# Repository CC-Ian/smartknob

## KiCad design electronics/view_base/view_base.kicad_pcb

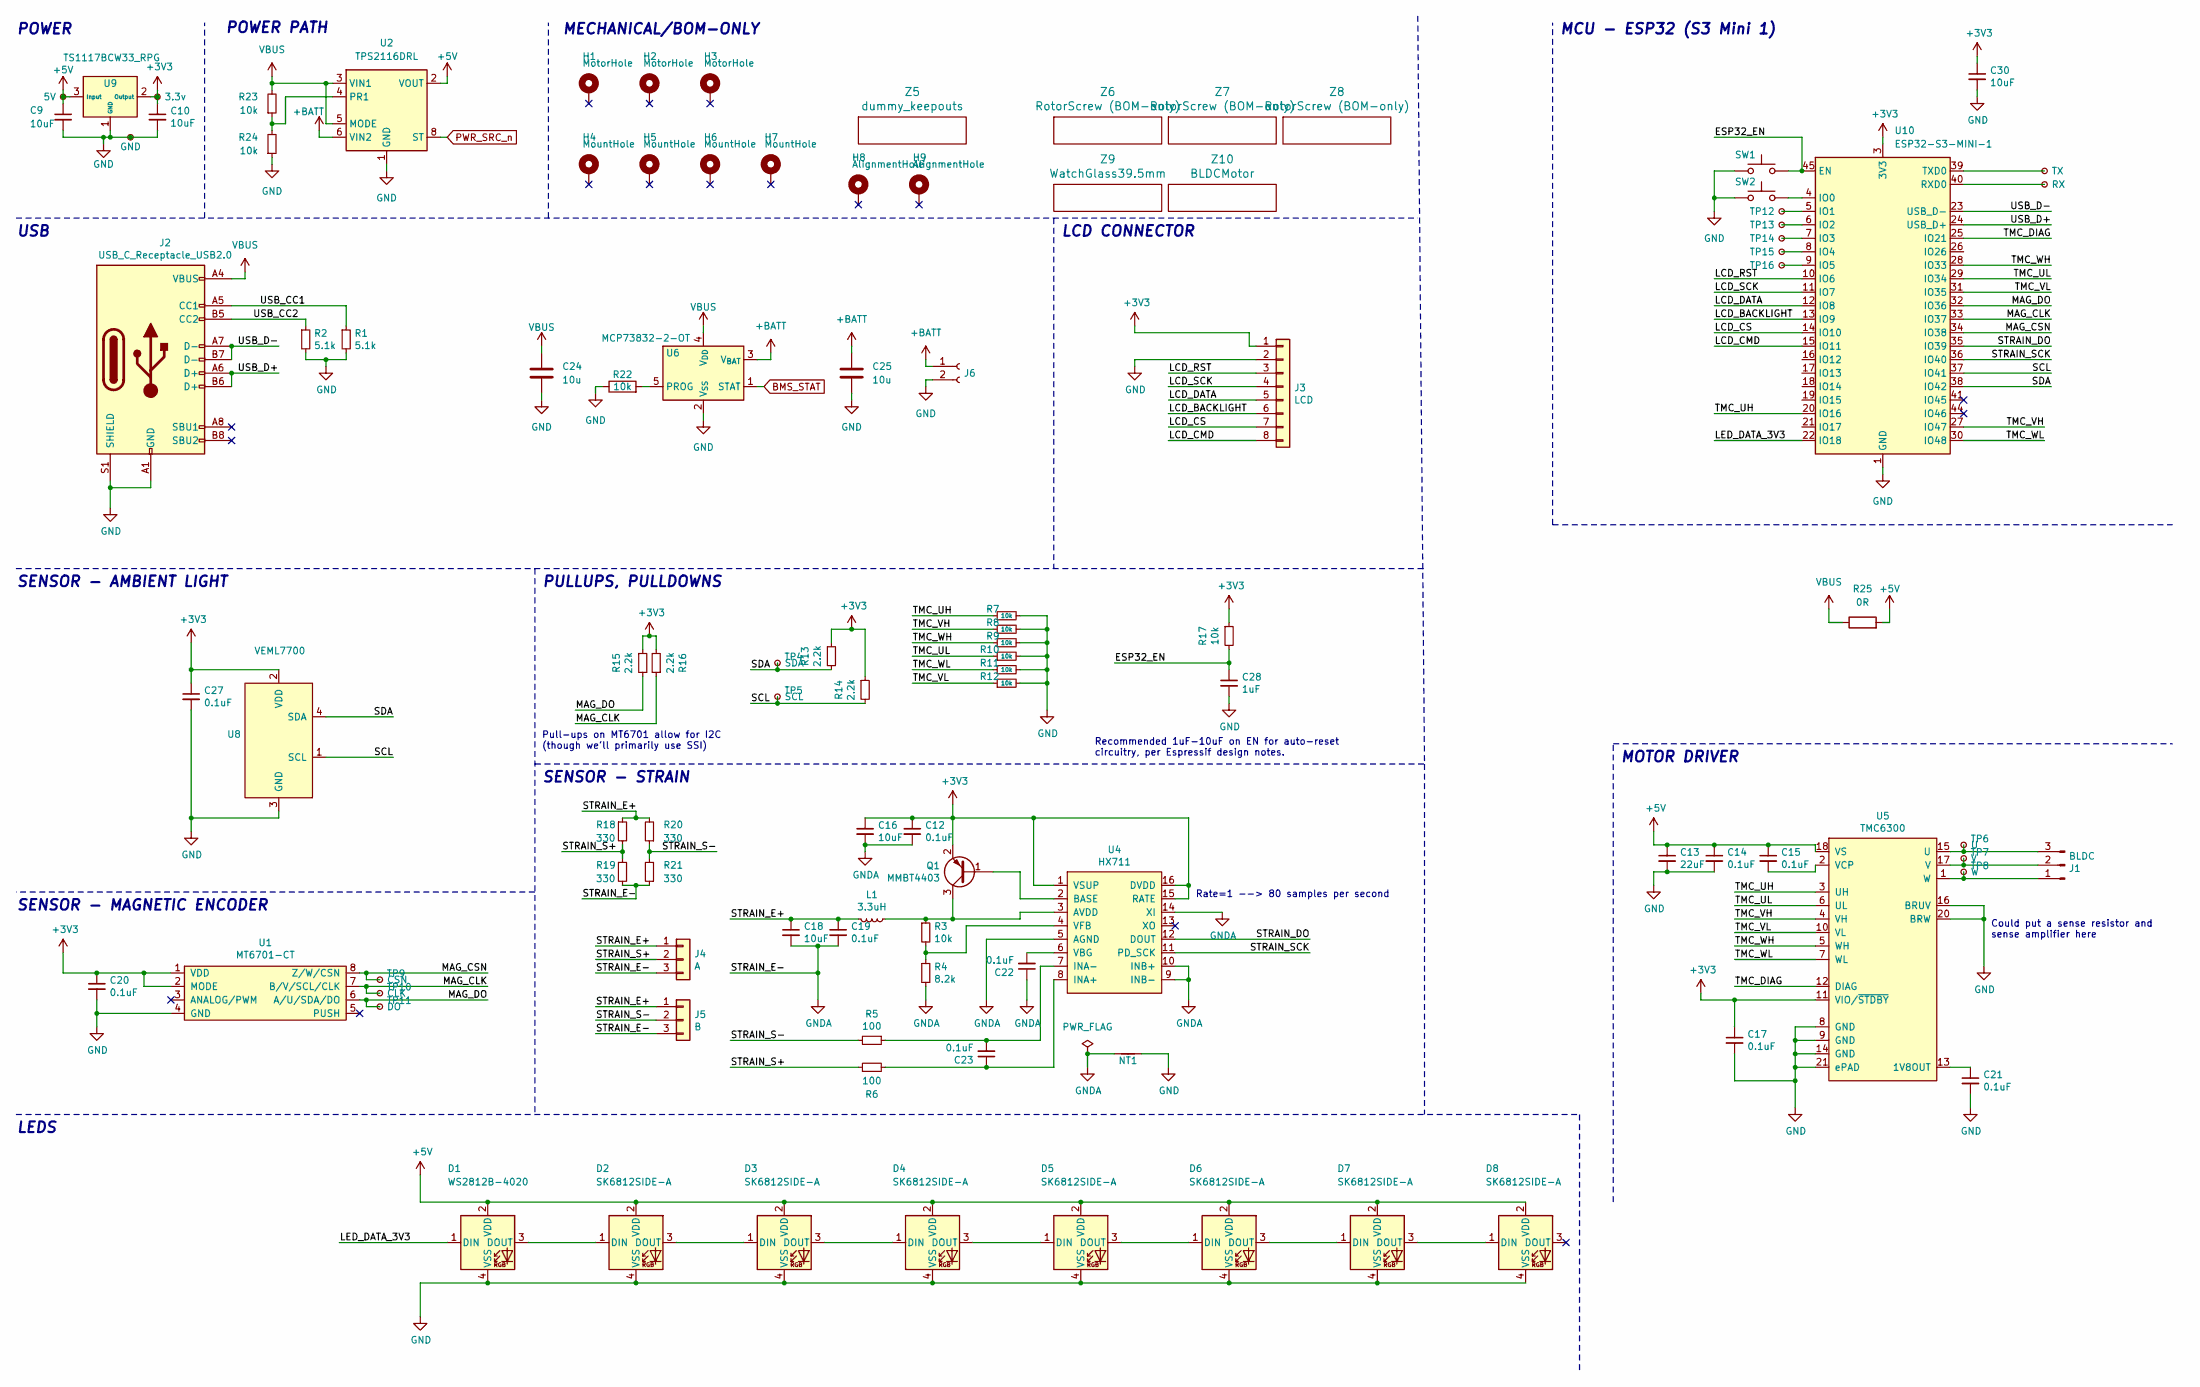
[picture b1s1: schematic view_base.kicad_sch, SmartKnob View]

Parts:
C9, C10, C16, C18, C30: 10uF; C_0603_1608Metric; LCSC C2922480
C12, C14, C15, C17, C19, C20, C21, C22, C23, C27: 0.1uF; C_0402_1005Metric; LCSC C1591
C13: 22uF; C_0603_1608Metric; LCSC C98190
C24, C25: 10u; C_0603_1608Metric
C28: 1uF; C_0402_1005Metric; Mouser 187-CL10A105KA8NNNC
D1: WS2812B-4020; WS2812B4020; Digikey 1528-4691-ND
D2, D3, D4, D5, D6, D7, D8: SK6812SIDE-A; WS2812B4020; Digikey 1528-4691-ND
H1, H2, H3: MotorHole; MountingHole_M1.6; LCSC C2931389
H4, H5, H6, H7: MountHole; MountingHole_2.2mm_M2_ISO7380_Pad_NonVirtual; LCSC C2911210 or C2911532 (screw), C2961595 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
H8, H9: AlignmentHole; MountingHole_2.2mm_M2_ISO7380_Pad_NonVirtual
J1: BLDC; 532610371; LCSC C293630
J2: USB_C_Receptacle_USB2.0; USB4510_NoPaste; LCSC C428463
J3: LCD; SolderPads_2mm_8
J4: A; SolderPads_2mm_3_STRAIN
J5: B; SolderPads_2mm_3_STRAIN
J6: Conn_01x02_Socket; PinHeader_1x02_P2.00mm_Vertical
L1: 3.3uH; L_0603_1608Metric; LCSC C307744
NT1: NetTie_2; NetTie-2_SMD_Pad0.5mm
Q1: MMBT4403; SOT-23; LCSC C78864
R1, R2: 5.1k; R_0402_1005Metric; LCSC C105580
R3, R7, R8, R9, R10, R11, R12, R17: 10k; R_0402_1005Metric; LCSC C98220
R4: 8.2k; R_0402_1005Metric; LCSC C114637
R5, R6: 100; R_0402_1005Metric; LCSC C319953
R13, R14, R15, R16: 2.2k; R_0402_1005Metric; LCSC C4190
R18, R19, R20, R21: 330; R_2512_6332Metric; LCSC C19866
R22, R23, R24: 10k; R_0402_1005Metric
R25: 0R; R_0603_1608Metric
SW1, SW2: SW_Push; T1B2QR
TP1: 5V; TestPoint_Pad_D2.0mm_ValueSilk
TP2: 3.3v; TestPoint_Pad_D2.0mm_ValueSilk
TP3: GND; TestPoint_Pad_D2.0mm_ValueSilk
TP4: SDA; TestPoint_Pad_D2.0mm_ValueSilk
TP5: SCL; TestPoint_Pad_D2.0mm_ValueSilk
TP6: U; TestPoint_Pad_D2.0mm_ValueSilk
TP7: V; TestPoint_Pad_D2.0mm_ValueSilk
TP8: W; TestPoint_Pad_D2.0mm_ValueSilk
TP9: CSN; TestPoint_Pad_D2.0mm_ValueSilk
TP10: CLK; TestPoint_Pad_D2.0mm_ValueSilk
TP11: DO; TestPoint_Pad_D2.0mm_ValueSilk
TP12, TP13, TP14, TP15, TP16: TestPoint_Small; TestPoint_Pad_D1.0mm
TP17: TX; TestPoint_Pad_D2.0mm_ValueSilk
TP18: RX; TestPoint_Pad_D2.0mm_ValueSilk
U1: MT6701-CT; SOIC-8_3.9x4.9mm_P1.27mm; LCSC C2856764, or C3003196
U2: TPS2116DRL; SOT-583-8; LCSC C3235557
U4: HX711; SOIC-16_3.9x9.9mm_P1.27mm; LCSC C43656
U5: TMC6300; QFN-20-1EP_3x3mm_P0.4mm_EP1.65x1.65mm; Digikey TMC6300-LA-T
U6: MCP73832-2-OT; SOT-23-5; LCSC C38066
U8: VEML7700; VEML7700-TOP; Digikey VEML7700-TT
U9: TS1117BCW33_RPG; SOT-223-3_TabPin2_GndOutIn; LCSC C6186
U10: ESP32-S3-MINI-1; ESP32-S2-MINI-1; LCSC C2913206
Z5: dummy_keepouts; ViewKeepouts3d
Z6, Z7, Z8: RotorScrew (BOM-only); bom_only_no_pin
Z9: WatchGlass39.5mm; bom_only_no_pin
Z10: BLDCMotor; bom_only_no_pin

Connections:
+3V3: C10.1, C12.1, C16.1, C17.1, C20.1, C27.1, C30.1, J3.1, Q1.2 (E), R13.1, R14.1, R15.1, R16.2, R17.1, TP2.1, U1.1 (VDD), U1.2 (MODE), U4.1 (VSUP), U4.15 (RATE), U4.16 (DVDD), U5.11 (VIO/~STDBY), U8.2 (VDD), U9.2 (Output), U10.3 (3V3)
+5V: C9.1, C13.1, C14.1, C15.1, D1.2 (VDD), D2.2 (VDD), D3.2 (VDD), D4.2 (VDD), D5.2 (VDD), D6.2 (VDD), D7.2 (VDD), D8.2 (VDD), R25.2, TP1.1, U2.2 (VOUT), U2.7 (VOUT), U5.18 (VS), U9.3 (Input)
+BATT: C25.1, J6.1, U2.6 (VIN2), U6.3 (V_{BAT})
/ESP32_EN: C28.1, R17.2, SW1.2, U10.45 (EN)
/LCD_BACKLIGHT: J3.6, U10.13 (IO9)
/LCD_CMD: J3.8, U10.15 (IO11)
/LCD_CS: J3.7, U10.14 (IO10)
/LCD_DATA: J3.5, U10.12 (IO8)
/LCD_RST: J3.3, U10.10 (IO6)
/LCD_SCK: J3.4, U10.11 (IO7)
/LED_DATA_3V3: D1.1 (DIN), U10.22 (IO18)
/MAG_CLK: R16.1, TP10.1, U1.7 (B/V/SCL/CLK), U10.33 (IO37)
/MAG_CSN: TP9.1, U1.8 (Z/W/CSN), U10.34 (IO38)
/MAG_DO: R15.2, TP11.1, U1.6 (A/U/SDA/DO), U10.32 (IO36)
/SCL: R14.2, TP5.1, U8.1 (SCL), U10.37 (IO41)
/SDA: R13.2, TP4.1, U8.4 (SDA), U10.38 (IO42)
/STRAIN_DO: U4.12 (DOUT), U10.35 (IO39)
/STRAIN_E+: C18.1, C19.1, J4.1, J5.1, L1.2, R18.1, R20.2
/STRAIN_S+: J4.2, R6.1, R18.2, R19.1
/STRAIN_S-: J5.2, R5.2, R20.1, R21.2
/STRAIN_SCK: U4.11 (PD_SCK), U10.36 (IO40)
/TMC_DIAG: U5.12 (DIAG), U10.25 (IO21)
/TMC_UH: R7.1, U5.3 (UH), U10.20 (IO16)
/TMC_UL: R10.1, U5.6 (UL), U10.29 (IO34)
/TMC_VH: R8.1, U5.4 (VH), U10.27 (IO47)
/TMC_VL: R12.1, U5.10 (VL), U10.31 (IO35)
/TMC_WH: R9.1, U5.5 (WH), U10.28 (IO33)
/TMC_WL: R11.1, U5.7 (WL), U10.30 (IO48)
/USB_CC1: J2.A5 (CC1), R1.1
/USB_CC2: J2.B5 (CC2), R2.1
/USB_D+: J2.A6 (D+), J2.B6 (D+), U10.24 (USB_D+)
/USB_D-: J2.A7 (D-), J2.B7 (D-), U10.23 (USB_D-)
BMS_STAT: U6.1 (STAT)
GND: C9.2, C10.2, C13.2, C14.2, C17.2, C20.2, C21.2, C24.2, C25.2, C27.2, C28.2, C30.2, D1.4 (VSS), D2.4 (VSS), D3.4 (VSS), D4.4 (VSS), D5.4 (VSS), D6.4 (VSS), D7.4 (VSS), D8.4 (VSS), J2.A1 (GND), J2.A12 (GND), J2.B1 (GND), J2.B12 (GND), J2.S1 (SHIELD), J3.2, J6.2, NT1.2, R1.2, R2.2, R7.2, R8.2, R9.2, R10.2, R11.2, R12.2, R22.1, R24.1, SW1.1, SW2.1, TP3.1, U1.4 (GND), U2.1 (GND), U5.8 (GND), U5.9 (GND), U5.14 (GND), U5.16 (BRUV), U5.20 (BRW), U5.21 (ePAD), U6.2 (V_{SS}), U8.3 (GND), U9.1 (GND), U10.1 (GND), U10.2 (GND), U10.42 (GND), U10.43 (GND), U10.46 (GND), U10.47 (GND), U10.48 (GND), U10.49 (GND), U10.50 (GND), U10.51 (GND), U10.52 (GND), U10.53 (GND), U10.54 (GND), U10.55 (GND), U10.56 (GND), U10.57 (GND), U10.58 (GND), U10.59 (GND), U10.60 (GND), U10.61 (GND), U10.62 (GND), U10.63 (GND), U10.64 (GND), U10.65 (GND)
GNDA: C12.2, C16.2, C18.2, C19.2, C22.1, J4.3, J5.3, NT1.1, R4.2, R19.2, R21.1, U4.5 (AGND), U4.9 (INB-), U4.10 (INB+), U4.14 (XI)
unnamed: D1.3 (DOUT), D2.1 (DIN)
unnamed: D2.3 (DOUT), D3.1 (DIN)
unnamed: D3.3 (DOUT), D4.1 (DIN)
unnamed: D4.3 (DOUT), D5.1 (DIN)
unnamed: D5.3 (DOUT), D6.1 (DIN)
unnamed: D6.3 (DOUT), D7.1 (DIN)
unnamed: D7.3 (DOUT), D8.1 (DIN)
unnamed: J1.1, TP8.1, U5.1 (W)
unnamed: J1.2, TP7.1, U5.17 (V)
unnamed: J1.3, TP6.1, U5.15 (U)
unnamed: Q1.1 (B), U4.2 (BASE)
unnamed: L1.1, Q1.3 (C), R3.1, U4.3 (AVDD)
unnamed: R23.1, R24.2, U2.4 (PR1)
unnamed: C23.1, R6.2, U4.8 (INA+)
unnamed: C23.2, R5.1, U4.7 (INA-)
unnamed: C22.2, U4.6 (VBG)
unnamed: R3.2, R4.1, U4.4 (VFB)
unnamed: C21.1, U5.13 (1V8OUT)
unnamed: C15.2, U5.2 (VCP)
unnamed: R22.2, U6.5 (PROG)
unnamed: SW2.2, U10.4 (IO0)
unnamed: TP12.1, U10.5 (IO1)
unnamed: TP13.1, U10.6 (IO2)
unnamed: TP14.1, U10.7 (IO3)
unnamed: TP15.1, U10.8 (IO4)
unnamed: TP16.1, U10.9 (IO5)
unnamed: TP18.1, U10.40 (RXD0)
unnamed: TP17.1, U10.39 (TXD0)
PWR_SRC_n: U2.8 (ST)
VBUS: C24.1, J2.A4 (VBUS), J2.A9 (VBUS), J2.B4 (VBUS), J2.B9 (VBUS), R23.2, R25.1, U2.3 (VIN1), U2.5 (MODE), U6.4 (V_{DD})

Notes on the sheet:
POWER PATH
MECHANICAL/BOM-ONLY
USB
Could put a sense resistor and sense amplifier here
Pull-ups on MT6701 allow for I2C (though we'll primarily use SSI)
SENSOR - MAGNETIC ENCODER
PULLUPS, PULLDOWNS
LEDS
Recommended 1uF-10uF on EN for auto-reset circuitry, per Espressif design notes.
MCU - ESP32 (S3 Mini 1)
LCD CONNECTOR
POWER
Rate=1 --> 80 samples per second
MOTOR DRIVER
SENSOR - AMBIENT LIGHT
SENSOR - STRAIN

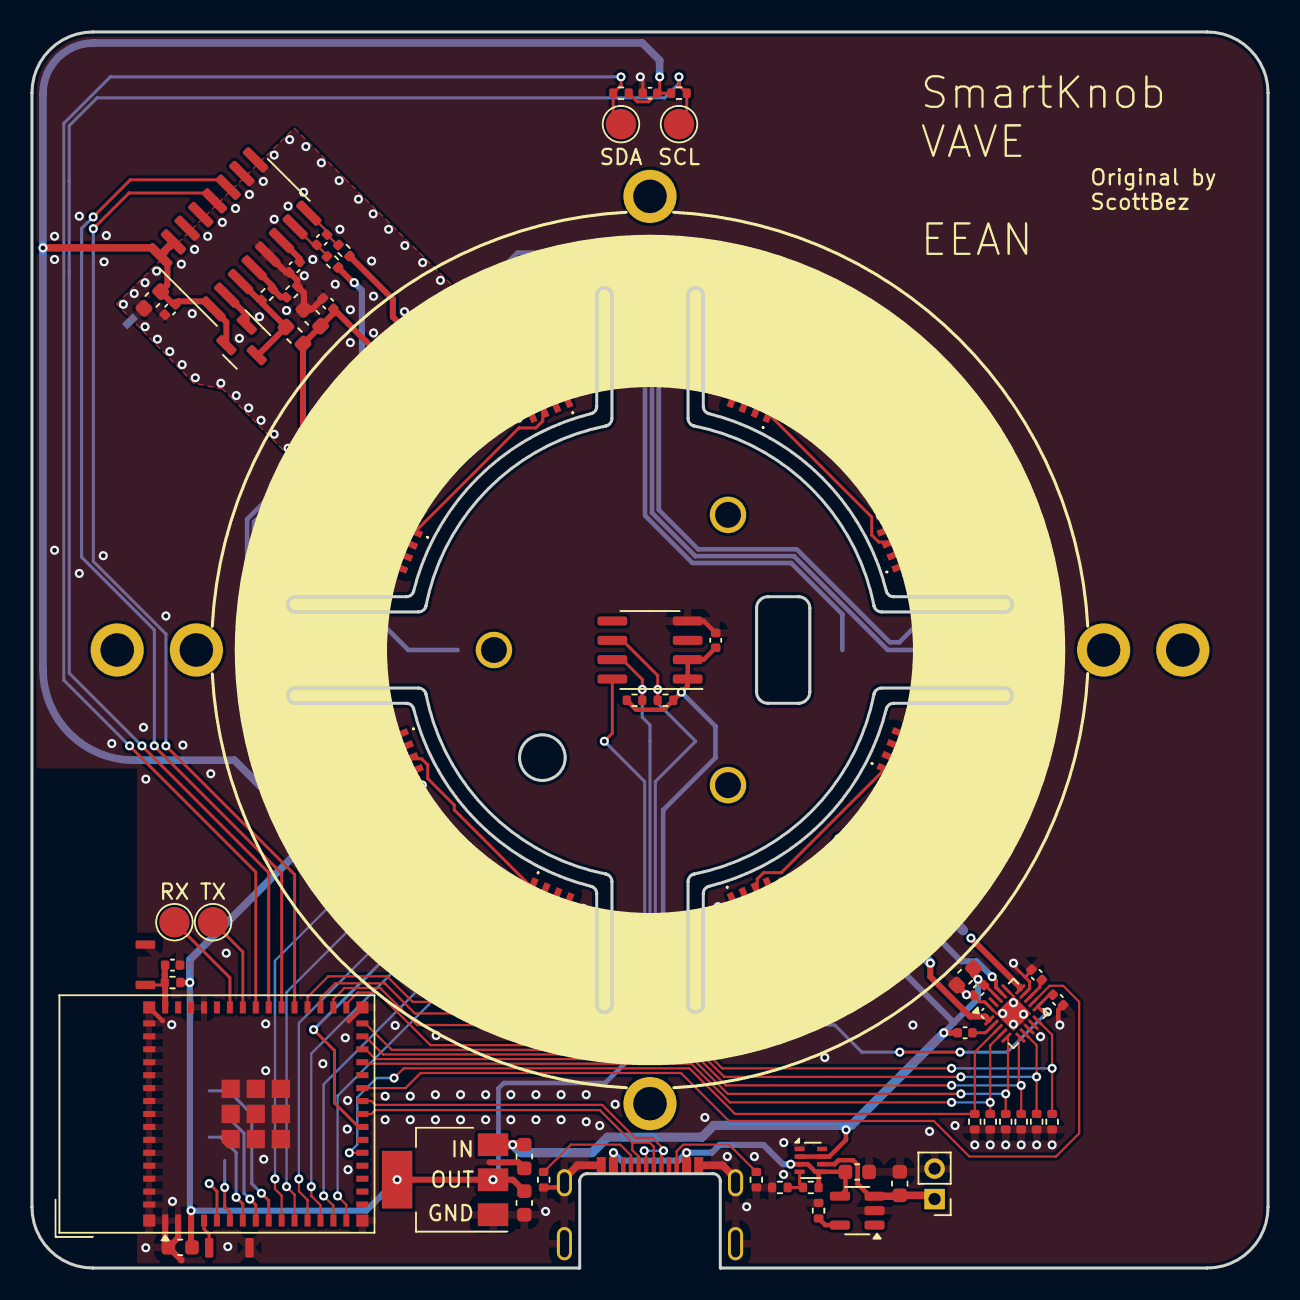
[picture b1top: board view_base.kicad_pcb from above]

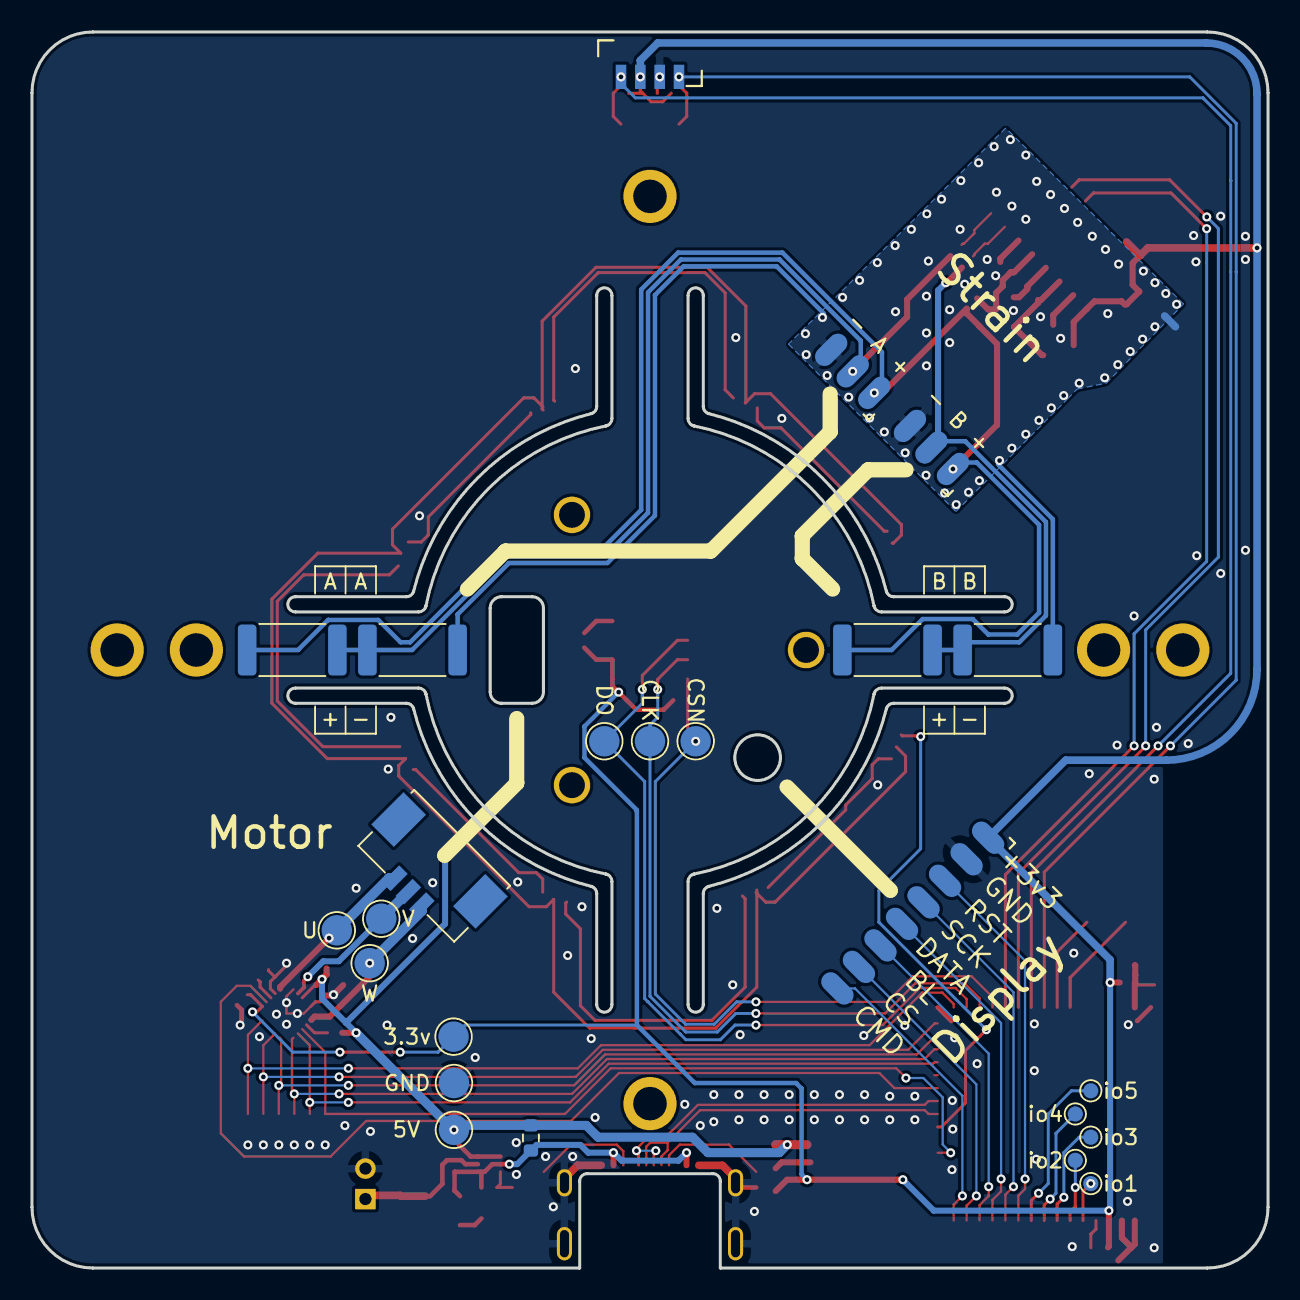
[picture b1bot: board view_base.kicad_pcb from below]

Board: 2 copper layers, 81.2 x 81.2 mm, 103 parts (25 on the bottom side), 63 nets.

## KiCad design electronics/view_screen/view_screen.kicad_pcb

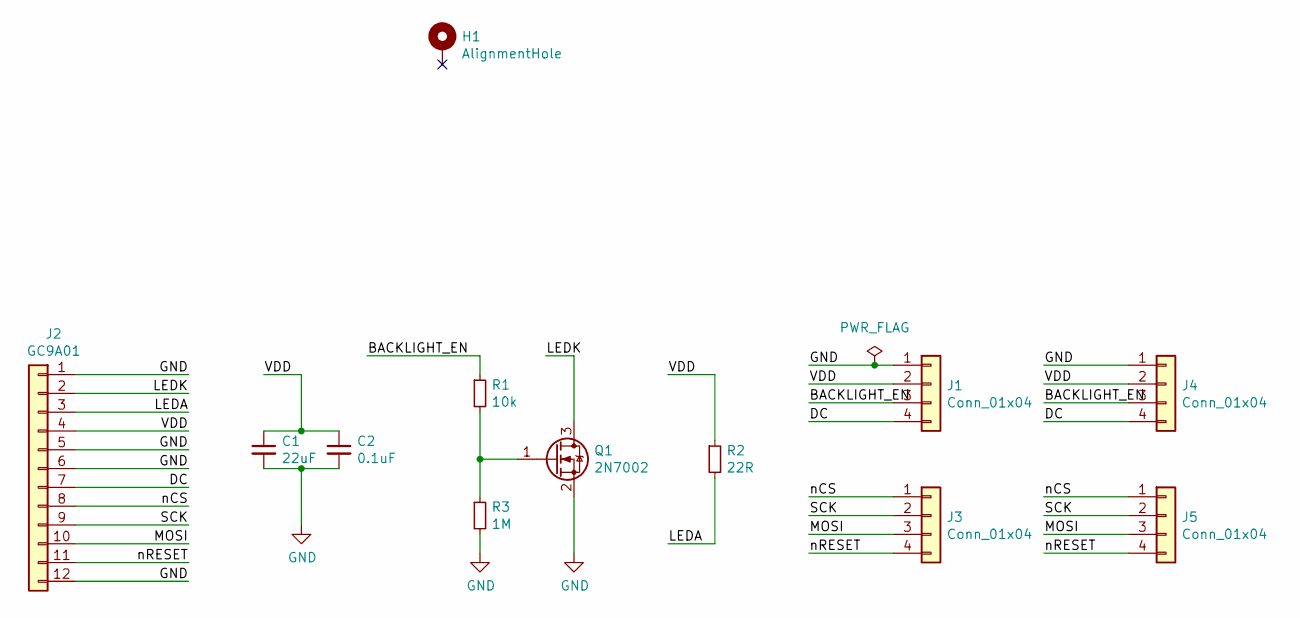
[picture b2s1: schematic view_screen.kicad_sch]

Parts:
C1: 22uF; C_0603_1608Metric; Digikey 1276-CL21A226MAYNNNECT-ND
C2: 0.1uF; C_0402_1005Metric; Digikey 1276-1935-1-ND
H1: AlignmentHole; AlignmentHole_1.6
J1, J3, J4, J5: Conn_01x04; SolderPads_2mm_4
J2: GC9A01; GC9A01Round1.28; Digikey N/A
Q1: 2N7002; SOT-23; Digikey 2N7002H6327XTSA2CT-ND
R1: 10k; R_0402_1005Metric; Digikey RMCF0603JT10K0CT-ND
R2: 22R; R_0402_1005Metric; Digikey RMCF0603JT22R0CT-ND
R3: 1M; R_0402_1005Metric; Digikey RMCF0603JT1M00CT-ND

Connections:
/BACKLIGHT_EN: J1.3, J4.3, R1.1
/DC: J1.4, J2.7, J4.4
/LEDA: J2.3, R2.2
/LEDK: J2.2, Q1.3 (D)
/MOSI: J2.10, J3.3, J5.3
/SCK: J2.9, J3.2, J5.2
/VDD: C1.1, C2.1, J1.2, J2.4, J4.2, R2.1
/nCS: J2.8, J3.1, J5.1
/nRESET: J2.11, J3.4, J5.4
GND: C1.2, C2.2, J1.1, J2.1, J2.5, J2.6, J2.12, J4.1, Q1.2 (S), R3.2
unnamed: Q1.1 (G), R1.2, R3.1

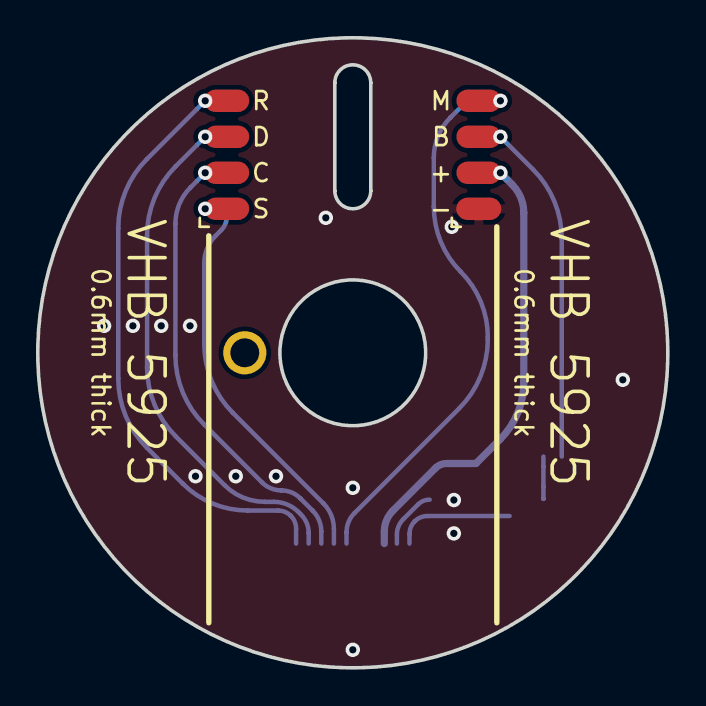
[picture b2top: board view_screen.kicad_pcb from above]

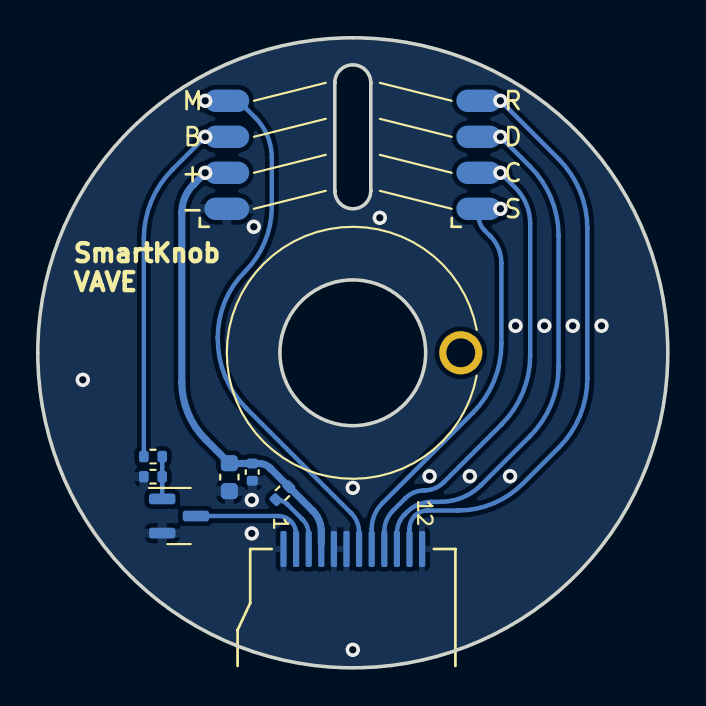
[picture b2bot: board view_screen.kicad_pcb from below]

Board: 2 copper layers, 35.0 x 35.0 mm, 12 parts (9 on the bottom side), 11 nets.

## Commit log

2025-03-25 Initial start
2025-03-28 Almost entirely completed vave
2025-03-30 Ordered Revision A
2025-04-29 Almost done. pending BOM

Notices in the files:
parts and their libraries:
Copyright 2021 Accelerated Designs. All rights reserved.
